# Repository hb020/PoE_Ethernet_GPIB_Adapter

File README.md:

# PoE Ethernet GPIB Adapter, with Prologix or VXI-11.2

## PoE-powered GPIB Adapter with Ethernet and USB-C Support

The **PoE Ethernet GPIB Adapter** is designed to interface test equipment with GPIB / HPIB / IEEE-488 interfaces.

The primary goal of this project is to provide an easy solution to connect multiple GPIB-equipped instruments over Ethernet without excessive cabling. It can, at choice, use the Prologix protocol or support VXI-11.2 (VISA).

---

## Why?

The motivation behind this project comes from the challenges of using several generations of instruments with GPIB interfaces. In theory, only one GPIB master is needed, and up to 20+ instruments can be connected in any order using suitable GPIB cabling. However, there are drawbacks:

- Instruments must be fully compliant with the IEEE-488 standard. Many older instruments, predating the standard, do not comply. The main issue is that the bus does not go Hi-Z when off, requiring certain instruments to be powered on even if you're only using another device.
- GPIB cabling is bulky and expensive. While used options can sometimes be found, the overall cost remains high.

At work, this has been solved elegantly using commercial Ethernet adapters, each assigned an address and connected directly to the instrument. However, these adapters are priced around $500 USD—far from hobbyist-friendly. My initial solution was to buy one adapter and rely on daisy-chaining, but as my instrument collection grew to 20 devices requiring GPIB, this approach was no longer practical. Hence, the **PoE Ethernet GPIB Adapter** was born.

---

## Design Criteria

1. Lower cost: Total BOM should be less than 50 USD.
2. Support Power over Ethernet (PoE) to minimize cable clutter.
3. Include USB-C power as an alternative if PoE is unavailable.
4. Enable GPIB communication over both Ethernet and USB-C interfaces.
5. Use the same communication protocol as existing commercial units.
6. Minimize radiated and conducted noise to avoid interference in test environments.
7. Include a simple, easy-to-print 3D-printed enclosure to keep costs low.

---

## Results

All design goals have been met[^2]. The current unit price is approximately $45 USD when ordering parts for 20 units. Prices increase for smaller batch sizes.

[^2]: GPIB commands over USB-C is Work In Progress.

In my home lab, I assign each device a static IP address based on its MAC address and run a local DNS server to provide easy-to-remember domain names, making the adapter simple and intuitive to use.

Project's documentation:

- [Design Documentation](docs/dn.md)
- [Design Test Documentation](docs/dt.md)

---

## VXI-11 or Prologix

This code can produce either a VXI-11.2 device, or a Prologix device (the ROM is not big enough for both at the same time, although the code is compatible with cohabitation). Switching between VXI-11 and Prologix is done at compile time. If compiler option `-DINTERFACE_PROLOGIX` is used, the firmware produced is for Prologix.

VXI-11.2 allows discovery over the network, and uses the following VISA connection strings:

- Controller[^1]: `TCPIP::{IP address}::INSTR` (unless you have set the default instrument address to something else than 0)
- Instruments: `TCPIP::{IP address}::gpib,N::INSTR` or `TCPIP::{IP address}::instN::INSTR`, where `N` is their address on the GPIB bus (1..30)

Example: `TCPIP::192.168.7.105::gpib,2::INSTR` for instrument with GPIB address 2 on the gateway having IP address 192.168.7.105.

[^1]: controller, gateway, adapter: different names for the same.

### VXI-11.2 compatibility

With the limited resources, this device is meant to work with the most common tools, like for example pyVisa. It is not a full implementation, and lacks the following advanced features:

- secondary instrument addresses
- async VXI-11 operations
- instrument locking via VXI-11
- VXI-11 interrupts
- the VXI-11 abort channel

It is discoverable via UDP, but there is no publication via mDNS (yet).

---

## The number of instruments you can connect

The GPIB bus protocol itself allows up to 30 instruments. This does not mean you can connect 30 instruments to the gateway, as the gateway device has its electrical limits, depending on the length of the cables and instruments themselves. And also the software has its limits.

The Prologix service will accept as many instruments as the gateway hardware can drive reliably.

The VXI-11 service is easier to integrate with many tools, but it consumes more resources on the gateway. The Ethernet chip can only maintain a limited number of network sockets, and each instrument requires a separate socket with VXI-11. Prologix uses only 1 socket, no matter the number of instruments. This means that regardless of the limitations of the hardware, there is a limit to the number of instruments you can connect to via VXI-11 compatible client software:

- up to 4 instruments: no restriction
- 5 instruments: only if you do not use the web server
- 6 instruments: only if you disable the web server (use the compile option `-DDISABLE_WEB_SERVER`)
- 7 or more: not possible via VXI-11

This does not mean that you cannot physically connect more instruments to the gateway, it just means that you cannot connect to more of them, via your client software, at the same time.

Also, be aware that the GPIB bus is a shared bus. Do not try to control instruments on the bus from different software clients at the same time. VXI-11 is somewhat more forgiving in this matter, but the prologix service simply doesn't allow multiple connections.

---

## The User Interface of the device

There are 3 parts:

- the **LED**. It indicates different states: blue for waiting for DHCP, red for error in network or DHCP, green flashing for idle, green/blue flashing for busy
- the **Web Server** (on port 80): it shows some help texts and the number of connected clients. It is not interactive.
- the **serial console** (via USB): This console shows startup information, ports used, and has a small menu. 

### The serial menu

This menu is rather basic. Be aware that it requires 'enter' for each command.

It has the following options:

- Setting of IP address. By default, the device starts with DHCP. You can however force a fixed IP address.
- Setting of the default instrument address (only with VXI-11, as Prologix has its own command for that). The default is 0, meaning: the gateway itself. If you only have 1 instrument connected, or want to designate a "preferred" instrument, you can set it to the address of any instrument on the bus. That way, the gateway becomes transparent, and you can use the default (and the discoverable) VISA connection string to address that instrument.

---

## Project files

Latest version is avaiable under [Releases](https://github.com/Kofen/PoE_Ethernet_GPIB_Adapter/releases)

And all the source code for all the parts should be in their respective folders in the repro. If anything is missing, let me know!

## How to compile

The easiest is for compilation with PlatformIO, from the [SW](/SW) directory.

## License

This project is licensed under the GPL V3. See the [LICENSE](LICENSE) file for details.

## Acknowledgements

- A huge thanks to the [AR488 project](https://github.com/Twilight-Logic/AR488), run by [Twilight-Logic](https://github.com/Twilight-Logic) and its community contributors. The current software is a fork of AR488. For more information about this, see [here](SW/README.md).

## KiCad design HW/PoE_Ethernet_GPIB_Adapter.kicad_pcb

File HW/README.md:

# PoE Ethernet GPIB Adapter - Hardware Files

## Overview

This folder contains the necessary hardware files for the PoE Ethernet GPIB Adapter project.

- **Schematics:** The schematic files can be found [here](https://github.com/Kofen/PoE_Ethernet_GPIB_Adapter/blob/main/HW/Schematic_PDF/PoE_Ethernet_GPIB_Adapter.pdf).
- **Output Files:** The output files, including Gerber files and assembly information, are located [here](https://github.com/Kofen/PoE_Ethernet_GPIB_Adapter/tree/main/HW/PoE_Ethernet_GPIB_Adapter_PCBA_MFG_Files).
- **Releases:** Precompiled hardware files for different versions are available under [Releases](https://github.com/Kofen/PoE_Ethernet_GPIB_Adapter/releases).

**Important note:** PCB thickness should be 1.6mm, 1 oz / 35 um copper thickness on all layers!

---

Ensure to verify compatibility with your PCB manufacturing service before using the files.

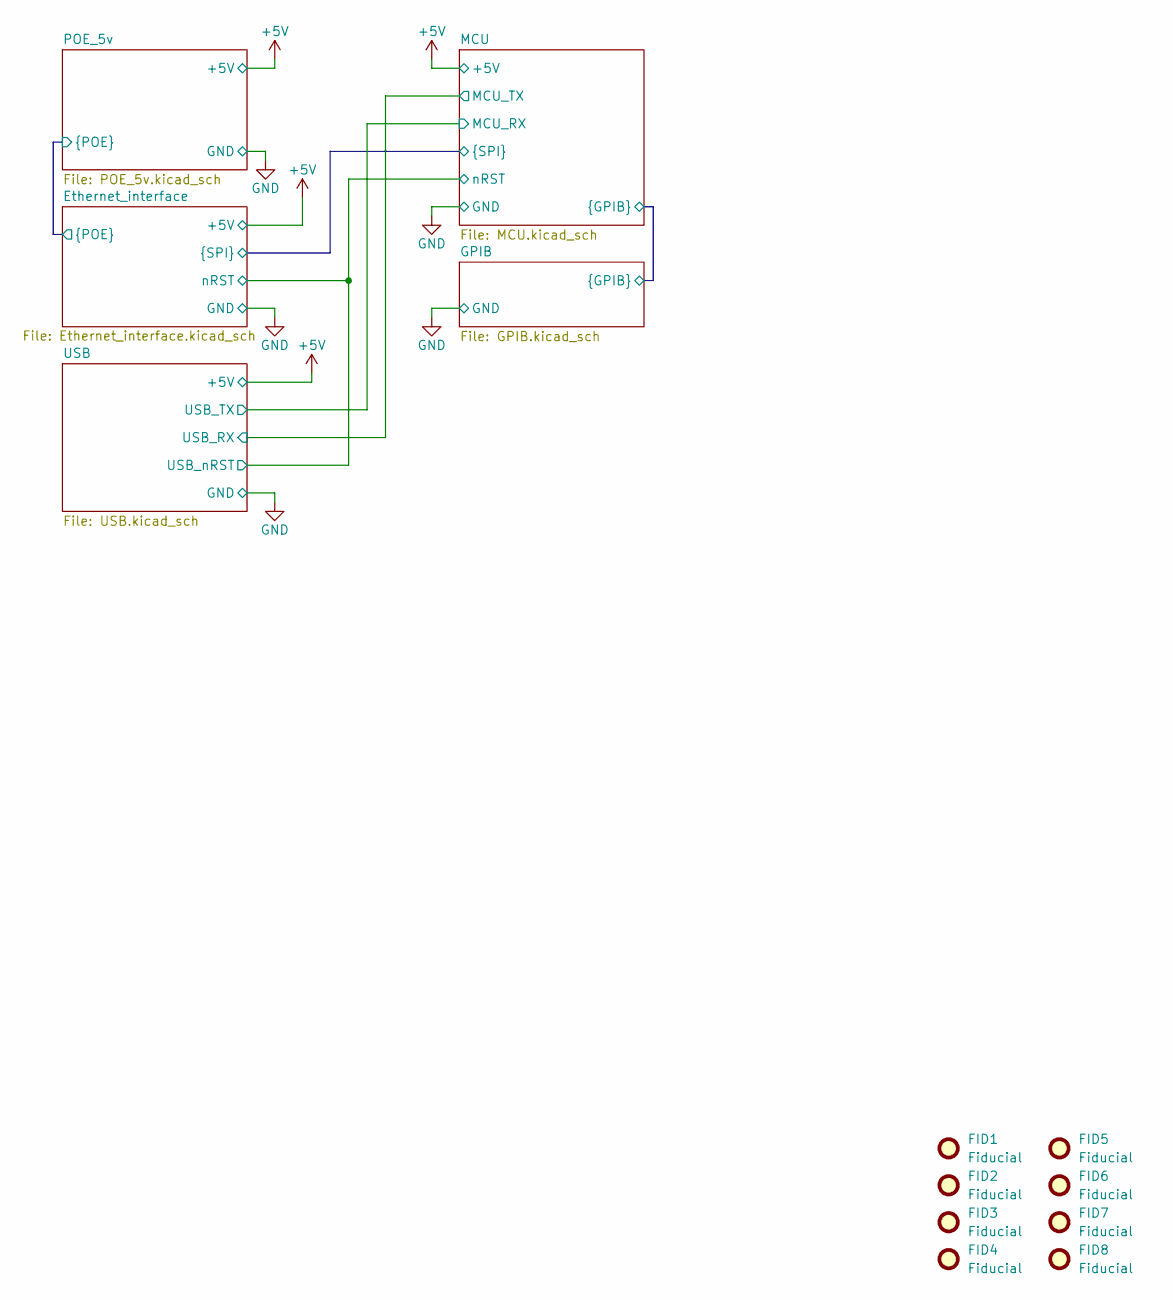
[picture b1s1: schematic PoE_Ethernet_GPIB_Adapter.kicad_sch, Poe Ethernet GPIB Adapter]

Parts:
FID1, FID2, FID3, FID4, FID5, FID6, FID7, FID8: Fiducial; Fiducial_0.75mm_Mask1.5mm

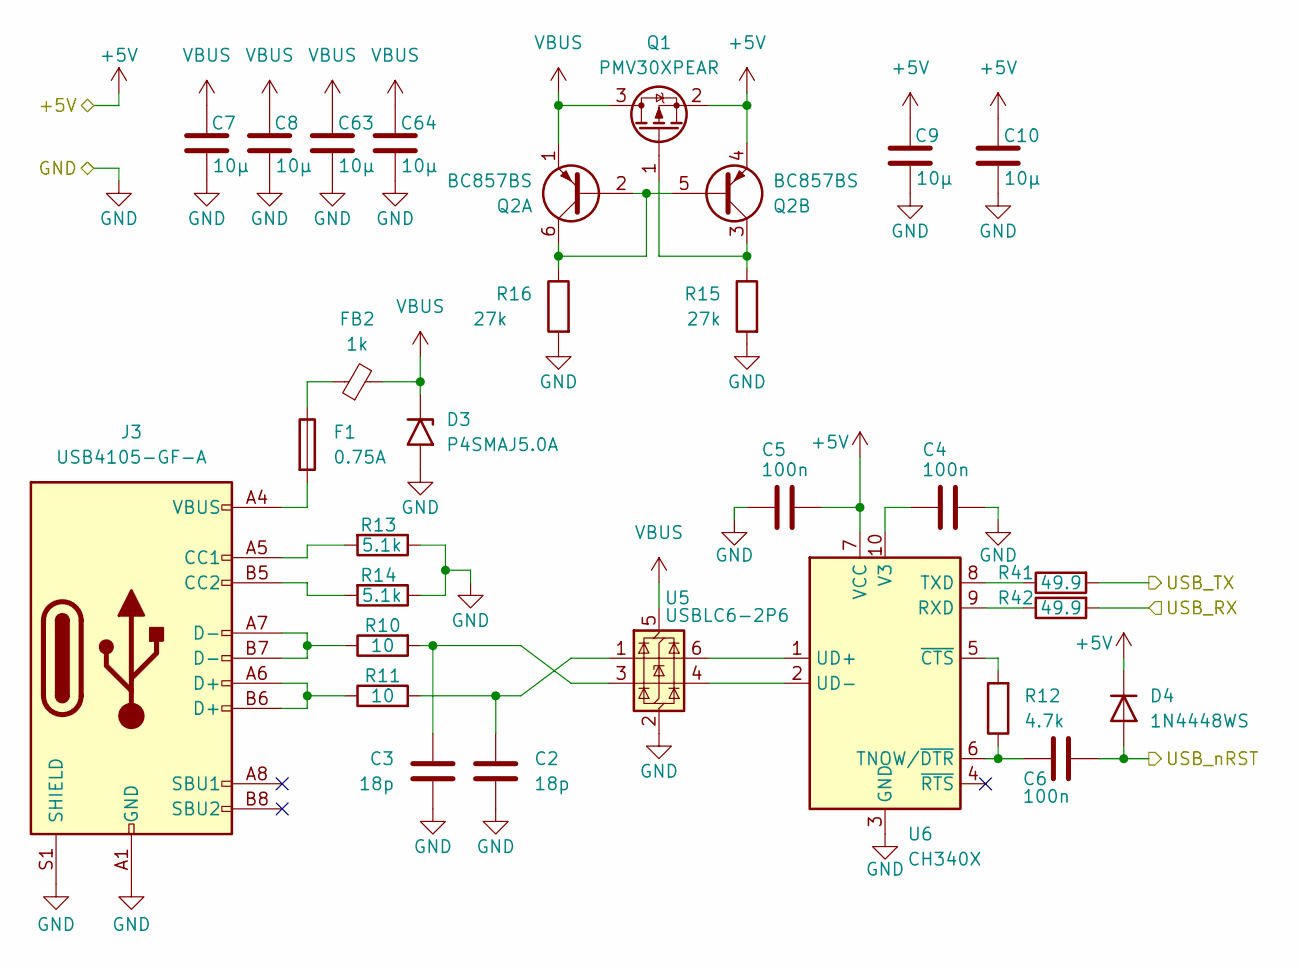
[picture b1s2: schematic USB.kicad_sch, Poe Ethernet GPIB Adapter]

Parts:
C2, C3: 18p; C_0402_1005Metric; JLCPCB C1549
C4, C5, C6: 100n; C_0402_1005Metric; JLCPCB C1525
C7, C8, C9, C10, C63, C64: 10µ; C_0402_1005Metric; JLCPCB C15525
D3: P4SMAJ5.0A; D_SMA; JLCPCB C391580
D4: 1N4448WS; D_SOD-323; JLCPCB C8602
F1: 0.75A; Fuse_1812_4532Metric; JLCPCB C3107
FB2: 1k; L_0805_2012Metric; JLCPCB C710395
J3: USB4105-GF-A; USB_C_Receptacle_GCT_USB4105-xx-A_16P_TopMnt_Horizontal; JLCPCB C3020560
Q1: PMV30XPEAR; SOT-23
Q2: BC857BS; SOT-363_SC-70-6
R10, R11: 10; R_0402_1005Metric
R12: 4.7k; R_0402_1005Metric
R13, R14: 5.1k; R_0402_1005Metric
R15, R16: 27k; R_0402_1005Metric
R41, R42: 49.9; R_0402_1005Metric
U5: USBLC6-2P6; SOT-666; JLCPCB C2827693
U6: CH340X; MSOP-10_3x3mm_P0.5mm; JLCPCB C3035748

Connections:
+5V: C5.2, C9.1, C10.1, D4.1 (K), Q1.2 (S), Q2.4 (E2), U6.7 (VCC); also elsewhere on the board
/Ethernet_interface/nRST: C6.2, D4.2 (A); also elsewhere on the board
/MCU/MCU_RX: R41.2; also elsewhere on the board
/MCU/MCU_TX: R42.2; also elsewhere on the board
GND: C2.2, C3.2, C4.2, C5.1, C7.2, C8.2, C9.2, C10.2, C63.2, C64.2, D3.2 (A2), J3.A1 (GND), J3.A12 (GND), J3.B1 (GND), J3.B12 (GND), J3.S1 (SHIELD), R13.1, R14.1, R15.2, R16.2, U5.2 (GND), U6.3 (GND); also elsewhere on the board
unnamed: C2.1, R11.2, U5.1 (I/O1)
unnamed: C3.1, R10.2, U5.3 (I/O2)
unnamed: F1.1, FB2.1
unnamed: F1.2, J3.A4 (VBUS), J3.A9 (VBUS), J3.B4 (VBUS), J3.B9 (VBUS)
unnamed: J3.A5 (CC1), R13.2
unnamed: J3.B5 (CC2), R14.2
unnamed: J3.A6 (D+), J3.B6 (D+), R11.1
unnamed: J3.A7 (D-), J3.B7 (D-), R10.1
unnamed: Q1.1 (G), Q2.3 (C2), R15.1
unnamed: Q2.2 (B1), Q2.5 (B2), Q2.6 (C1), R16.1
unnamed: R42.1, U6.9 (RXD)
unnamed: C6.1, R12.1, U6.6 (TNOW/~DTR)
unnamed: R41.1, U6.8 (TXD)
unnamed: U5.6 (I/O1), U6.1 (UD+)
unnamed: U5.4 (I/O2), U6.2 (UD-)
unnamed: C4.1, U6.10 (V3)
unnamed: R12.2, U6.5 (~CTS)
VBUS: C7.1, C8.1, C63.1, C64.1, D3.1 (A1), FB2.2, Q1.3 (D), Q2.1 (E1), U5.5 (VBUS)

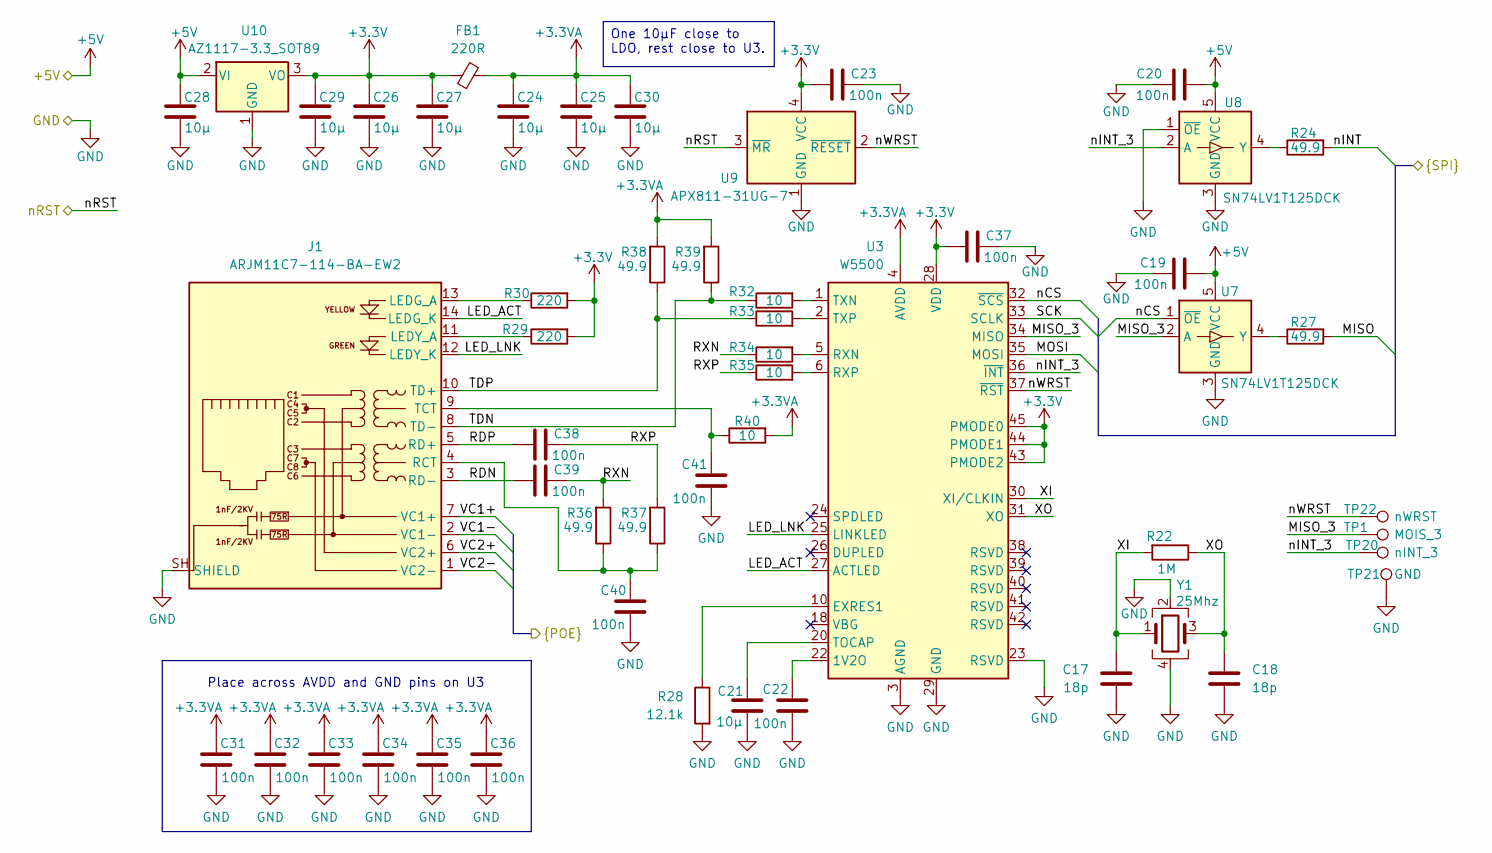
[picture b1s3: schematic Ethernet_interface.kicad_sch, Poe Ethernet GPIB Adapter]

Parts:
C17, C18: 18p; C_0402_1005Metric; JLCPCB C1549
C19, C20, C22, C23, C31, C32, C33, C34, C35, C36, C37, C38, C39, C40, C41: 100n; C_0402_1005Metric; JLCPCB C1525
C21, C24, C25, C26, C27, C28, C29, C30: 10µ; C_0402_1005Metric; JLCPCB C15525
FB1: 220R; L_0603_1608Metric; JLCPCB C139471
J1: ARJM11C7-114-BA-EW2; RJ45_ARJM11C7-114-BA-EW2
R22: 1M; R_0402_1005Metric
R24, R27, R36, R37, R38, R39: 49.9; R_0402_1005Metric
R28: 12.1k; R_0402_1005Metric
R29, R30: 220; R_0402_1005Metric
R32, R33, R34, R35, R40: 10; R_0402_1005Metric
TP1: MOIS_3; TestPoint_Pad_D1.0mm
TP20: nINT_3; TestPoint_Pad_D1.0mm
TP21: GND; TestPoint_Pad_D1.0mm
TP22: nWRST; TestPoint_Pad_D1.0mm
U3: W5500; LQFP-48_7x7mm_P0.5mm; JLCPCB C32843
U7, U8: SN74LV1T125DCK; SOT-353_SC-70-5; JLCPCB C2859742
U9: APX811-31UG-7; SOT-143; JLCPCB C150481
U10: AZ1117-3.3_SOT89; SOT-89-3; JLCPCB C362111
Y1: 25Mhz; Crystal_SMD_2520-4Pin_2.5x2.0mm; JLCPCB C5727305

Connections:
+3.3V: C23.2, C26.1, C27.1, C29.1, C37.2, FB1.1, R29.2, R30.2, U3.28 (VDD), U3.43 (PMODE2), U3.44 (PMODE1), U3.45 (PMODE0), U9.4 (VCC), U10.3 (VO)
+3.3VA: C24.1, C25.1, C30.1, C31.2, C32.2, C33.2, C34.2, C35.2, C36.2, FB1.2, R38.2, R39.2, R40.2, U3.4 (AVDD), U3.8 (AVDD), U3.11 (AVDD), U3.15 (AVDD), U3.17 (AVDD), U3.21 (AVDD)
+5V: C19.2, C20.2, C28.1, U7.5 (VCC), U8.5 (VCC), U10.2 (VI); also elsewhere on the board
/Ethernet_interface/LED_ACT: J1.14 (LEDG_K), U3.27 (ACTLED)
/Ethernet_interface/LED_LNK: J1.12 (LEDY_K), U3.25 (LINKLED)
/Ethernet_interface/MISO: R27.2; also elsewhere on the board
/Ethernet_interface/MISO_3: TP1.1, U3.34 (MISO), U7.2 (A)
/Ethernet_interface/MOSI: U3.35 (MOSI); also elsewhere on the board
/Ethernet_interface/RDN: C39.2, J1.3 (RD-)
/Ethernet_interface/RDP: C38.2, J1.5 (RD+)
/Ethernet_interface/RXN: C39.1, R34.1, R36.2
/Ethernet_interface/RXP: C38.1, R35.1, R37.2
/Ethernet_interface/SCK: U3.33 (SCLK); also elsewhere on the board
/Ethernet_interface/TDN: J1.8 (TD-), R32.1, R39.1
/Ethernet_interface/TDP: J1.10 (TD+), R33.1, R38.1
/Ethernet_interface/VC1+: J1.7 (VC1+); also elsewhere on the board
/Ethernet_interface/VC1-: J1.2 (VC1-); also elsewhere on the board
/Ethernet_interface/VC2+: J1.6 (VC2+); also elsewhere on the board
/Ethernet_interface/VC2-: J1.1 (VC2-); also elsewhere on the board
/Ethernet_interface/XI: C17.1, R22.2, U3.30 (XI/CLKIN), Y1.1
/Ethernet_interface/XO: C18.1, R22.1, U3.31 (XO), Y1.3
/Ethernet_interface/nCS: U3.32 (~SCS), U7.1 (~OE); also elsewhere on the board
/Ethernet_interface/nINT: R24.2; also elsewhere on the board
/Ethernet_interface/nINT_3: TP20.1, U3.36 (~INT), U8.2 (A)
/Ethernet_interface/nRST: U9.3 (~MR); also elsewhere on the board
/Ethernet_interface/nWRST: TP22.1, U3.37 (~RST), U9.2 (~RESET)
GND: C17.2, C18.2, C19.1, C20.1, C21.2, C22.1, C23.1, C24.2, C25.2, C26.2, C27.2, C28.2, C29.2, C30.2, C31.1, C32.1, C33.1, C34.1, C35.1, C36.1, C37.1, C40.1, C41.1, J1.SH (SHIELD), R28.2, TP21.1, U3.3 (AGND), U3.9 (AGND), U3.14 (AGND), U3.16 (AGND), U3.19 (AGND), U3.23 (RSVD), U3.29 (GND), U3.48 (AGND), U7.3 (GND), U8.1 (~OE), U8.3 (GND), U9.1 (GND), U10.1 (GND), Y1.2, Y1.4; also elsewhere on the board
unnamed: J1.13 (LEDG_A), R30.1
unnamed: J1.11 (LEDY_A), R29.1
unnamed: C40.2, J1.4 (RCT), R36.1, R37.1
unnamed: C41.2, J1.9 (TCT), R40.1
unnamed: C22.2, U3.22 (1V2O)
unnamed: R28.1, U3.10 (EXRES1)
unnamed: R34.2, U3.5 (RXN)
unnamed: R35.2, U3.6 (RXP)
unnamed: C21.1, U3.20 (TOCAP)
unnamed: R32.2, U3.1 (TXN)
unnamed: R33.2, U3.2 (TXP)
unnamed: R27.1, U7.4 (Y)
unnamed: R24.1, U8.4 (Y)

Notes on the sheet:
Place across AVDD and GND pins on U3
One 10µF close to LDO, rest close to U3.

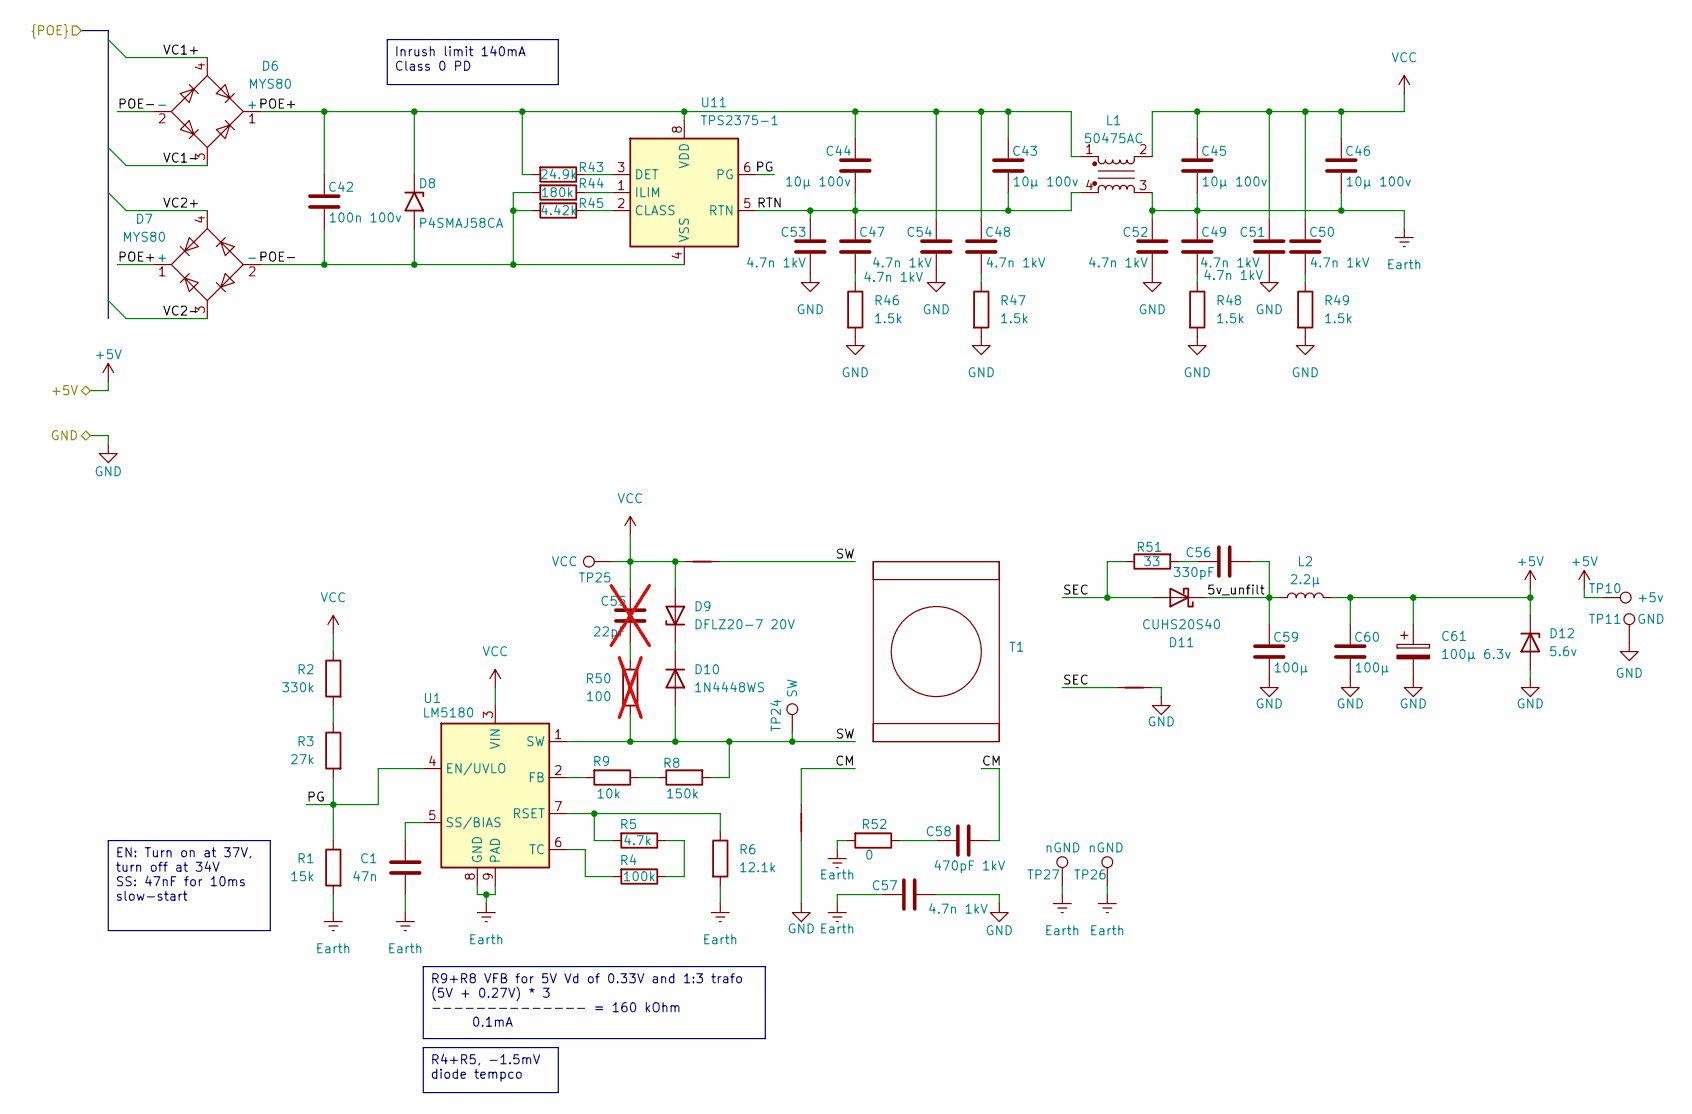
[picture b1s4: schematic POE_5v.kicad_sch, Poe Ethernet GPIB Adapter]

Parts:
C1: 47n; C_0402_1005Metric; JLCPCB C82219
C42: 100n 100v; C_0603_1608Metric; JLCPCB C15725
C43, C44, C45, C46: 10µ 100v; C_1210_3225Metric; JLCPCB C5156756
C47, C48, C49, C50, C51, C52, C53, C54, C57: 4.7n 1kV; C_0805_2012Metric; JLCPCB C565695
C55: 22pF; C_0603_1608Metric; not fitted
C56: 330pF; C_0603_1608Metric; JLCPCB C458879
C58: 470pF 1kV; C_0805_2012Metric; JLCPCB C20416464
C59, C60: 100µ; C_1206_3216Metric; JLCPCB CL31A107MQHNNNE
C61: 100µ 6.3v; CP_Elec_5x5.3; JLCPCB C5530352
D6, D7: MYS80; Diode_Bridge_Diotec_MicroDil_3.0x3.0x1.8mm; JLCPCB C3589669
D8: P4SMAJ58CA; D_SMA; JLCPCB C268635
D9: DFLZ20-7 20V; D_PowerDI-123; JLCPCB C177024
D10: 1N4448WS; D_SOD-323; JLCPCB C8602
D11: CUHS20S40; D_TUMD2; JLCPCB C3758140
D12: 5.6v; D_SOD-123F; JLCPCB C2119
L1: 50475AC; muRata_5000A
L2: 2.2µ; L_Taiyo-Yuden_NR-50xx
NT1, NT2: NetTie_2; NetTie-2_SMD_Pad0.5mm
NT3: NetTie_2; NetTie-2_SMD_Pad0.8mm
R1: 15k; R_0402_1005Metric
R2: 330k; R_0805_2012Metric
R3: 27k; R_0402_1005Metric
R4: 100k; R_0402_1005Metric
R5: 4.7k; R_0402_1005Metric
R6: 12.1k; R_0402_1005Metric
R8: 150k; R_0805_2012Metric
R9: 10k; R_0402_1005Metric
R43: 24.9k; R_0402_1005Metric
R44: 180k; R_0402_1005Metric
R45: 4.42k; R_0402_1005Metric
R46, R47, R48, R49: 1.5k; R_0603_1608Metric
R50: 100; R_0603_1608Metric; not fitted
R51: 33; R_0603_1608Metric
R52: 0; R_0603_1608Metric
T1: ER14_planar_4_to_1_48v_in_5v_out_5w
TP10: +5v; TestPoint_Pad_D1.0mm
TP11: GND; TestPoint_Pad_D1.0mm
TP24: SW; TestPoint_Pad_D1.0mm
TP25: VCC; TestPoint_Pad_D1.0mm
TP26, TP27: nGND; TestPoint_Pad_D1.0mm
U1: LM5180; WSON-8-1EP_4x4mm_P0.8mm_EP1.98x3mm; JLCPCB C2868878
U11: TPS2375-1; TSSOP-8_4.4x3mm_P0.65mm; JLCPCB C2859774

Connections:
+5V: C60.1, C61.1, D12.1 (K), L2.2, TP10.1; also elsewhere on the board
/Ethernet_interface/VC1+: D6.4; also elsewhere on the board
/Ethernet_interface/VC1-: D6.3; also elsewhere on the board
/Ethernet_interface/VC2+: D7.4; also elsewhere on the board
/Ethernet_interface/VC2-: D7.3; also elsewhere on the board
/POE_5v/5v_unfilt: C56.2, C59.1, D11.1 (K), L2.1
/POE_5v/CM: C58.1, NT2.2
/POE_5v/PG: R1.1, R3.2, U1.4 (EN/UVLO), U11.6 (PG)
/POE_5v/POE+: C42.1, C43.1, C44.1, C48.1, C54.1, D6.1 (+), D7.1 (+), D8.1 (A1), L1.1, R43.2, U11.8 (VDD)
/POE_5v/POE-: C42.2, D6.2 (-), D7.2 (-), D8.2 (A2), R44.2, R45.2, U11.4 (VSS)
/POE_5v/RTN: C43.2, C44.2, C47.1, C53.1, L1.4, U11.5 (RTN)
/POE_5v/SEC: D11.2 (A), NT3.1, R51.1
/POE_5v/SW: D10.2 (A), NT1.2, R8.2, R50.2, TP24.1, U1.1 (SW)
Earth: C1.2, C45.2, C46.2, C49.1, C52.1, C57.2, L1.3, R1.2, R6.2, R52.2, TP26.1, TP27.1, U1.8 (GND), U1.9 (PAD)
GND: C51.2, C52.2, C53.2, C54.2, C57.1, C59.2, C60.2, C61.2, D12.2 (A), NT2.1, NT3.2, R46.2, R47.2, R48.2, R49.2, TP11.1; also elsewhere on the board
unnamed: C47.2, R46.1
unnamed: C48.2, R47.1
unnamed: C49.2, R48.1
unnamed: C50.2, R49.1
unnamed: C55.2, R50.1
unnamed: C56.1, R51.2
unnamed: C58.2, R52.1
unnamed: D9.1 (K), D10.1 (K)
unnamed: R2.2, R3.1
unnamed: R4.1, R5.1
unnamed: R8.1, R9.1
unnamed: R9.2, U1.2 (FB)
unnamed: R5.2, R6.1, U1.7 (RSET)
unnamed: C1.1, U1.5 (SS/BIAS)
unnamed: R4.2, U1.6 (TC)
unnamed: R45.1, U11.2 (CLASS)
unnamed: R43.1, U11.3 (DET)
unnamed: R44.1, U11.1 (ILIM)
VCC: C45.1, C46.1, C50.1, C51.1, C55.1, D9.2 (A), L1.2, NT1.1, R2.1, TP25.1, U1.3 (VIN)

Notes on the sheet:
R9+R8 VFB for 5V Vd of 0.33V and 1:3 trafo (5V + 0.27V) * 3 -------------- = 160 kOhm 0.1mA
R4+R5, -1.5mV diode tempco
EN: Turn on at 37V, turn off at 34V SS: 47nF for 10ms slow-start
Inrush limit 140mA Class 0 PD

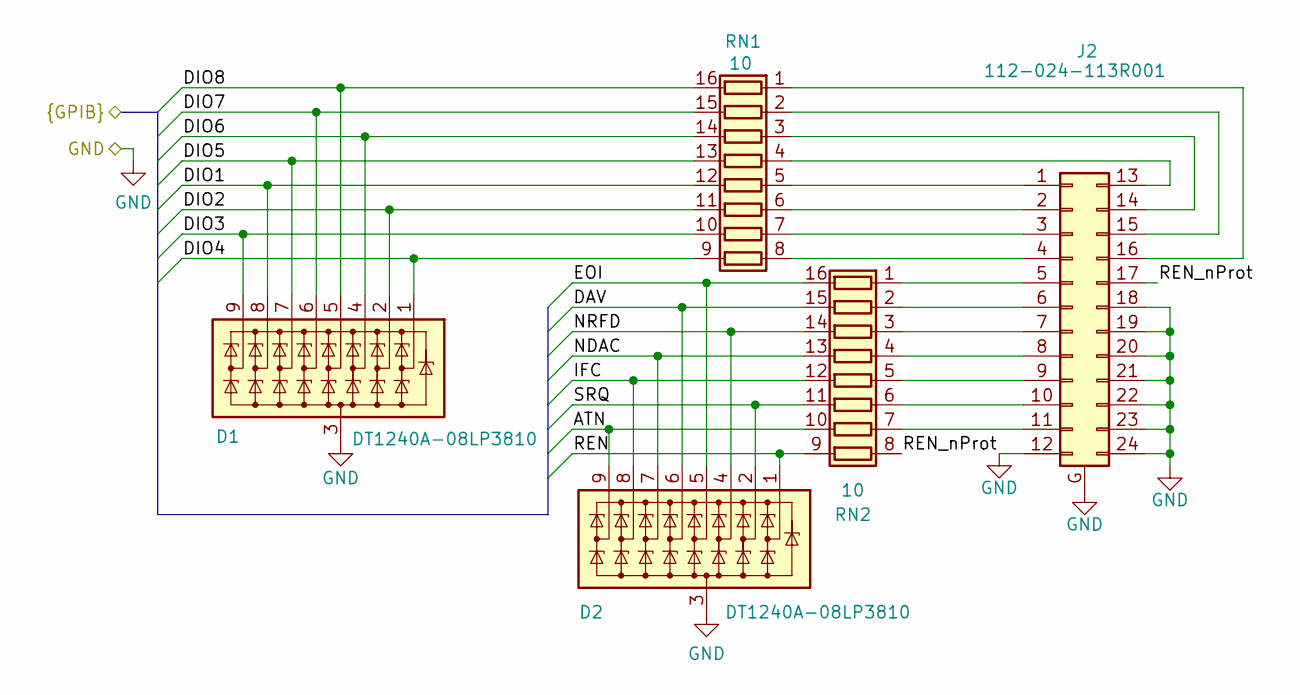
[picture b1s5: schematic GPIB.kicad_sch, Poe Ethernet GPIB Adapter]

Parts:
D1, D2: DT1240A-08LP3810; UDFN-9_1.0x3.8mm_P0.5mm; JLCPCB C526598
J2: 112-024-113R001
RN1, RN2: 10; R_Array_Convex_8x0602; JLCPCB C1518172

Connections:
/GPIB/ATN: D2.9 (K8), RN2.10 (R7.2); also elsewhere on the board
/GPIB/DAV: D2.6 (K5), RN2.15 (R2.2); also elsewhere on the board
/GPIB/DIO1: D1.8 (K7), RN1.12 (R5.2); also elsewhere on the board
/GPIB/DIO2: D1.2 (K2), RN1.11 (R6.2); also elsewhere on the board
/GPIB/DIO3: D1.9 (K8), RN1.10 (R7.2); also elsewhere on the board
/GPIB/DIO4: D1.1 (K1), RN1.9 (R8.2); also elsewhere on the board
/GPIB/DIO5: D1.7 (K6), RN1.13 (R4.2); also elsewhere on the board
/GPIB/DIO6: D1.4 (K3), RN1.14 (R3.2); also elsewhere on the board
/GPIB/DIO7: D1.6 (K5), RN1.15 (R2.2); also elsewhere on the board
/GPIB/DIO8: D1.5 (K4), RN1.16 (R1.2); also elsewhere on the board
/GPIB/EOI: D2.5 (K4), RN2.16 (R1.2); also elsewhere on the board
/GPIB/IFC: D2.8 (K7), RN2.12 (R5.2); also elsewhere on the board
/GPIB/NDAC: D2.7 (K6), RN2.13 (R4.2); also elsewhere on the board
/GPIB/NRFD: D2.4 (K3), RN2.14 (R3.2); also elsewhere on the board
/GPIB/REN: D2.1 (K1), RN2.9 (R8.2); also elsewhere on the board
/GPIB/REN_nProt: J2.17, RN2.8 (R8.1)
/GPIB/SRQ: D2.2 (K2), RN2.11 (R6.2); also elsewhere on the board
GND: D1.3 (A), D2.3 (A), J2.12, J2.18, J2.19, J2.20, J2.21, J2.22, J2.23, J2.24, J2.G (Chassis); also elsewhere on the board
unnamed: J2.1, RN1.5 (R5.1)
unnamed: J2.2, RN1.6 (R6.1)
unnamed: J2.3, RN1.7 (R7.1)
unnamed: J2.4, RN1.8 (R8.1)
unnamed: J2.5, RN2.1 (R1.1)
unnamed: J2.6, RN2.2 (R2.1)
unnamed: J2.7, RN2.3 (R3.1)
unnamed: J2.8, RN2.4 (R4.1)
unnamed: J2.9, RN2.5 (R5.1)
unnamed: J2.10, RN2.6 (R6.1)
unnamed: J2.11, RN2.7 (R7.1)
unnamed: J2.13, RN1.4 (R4.1)
unnamed: J2.14, RN1.3 (R3.1)
unnamed: J2.15, RN1.2 (R2.1)
unnamed: J2.16, RN1.1 (R1.1)

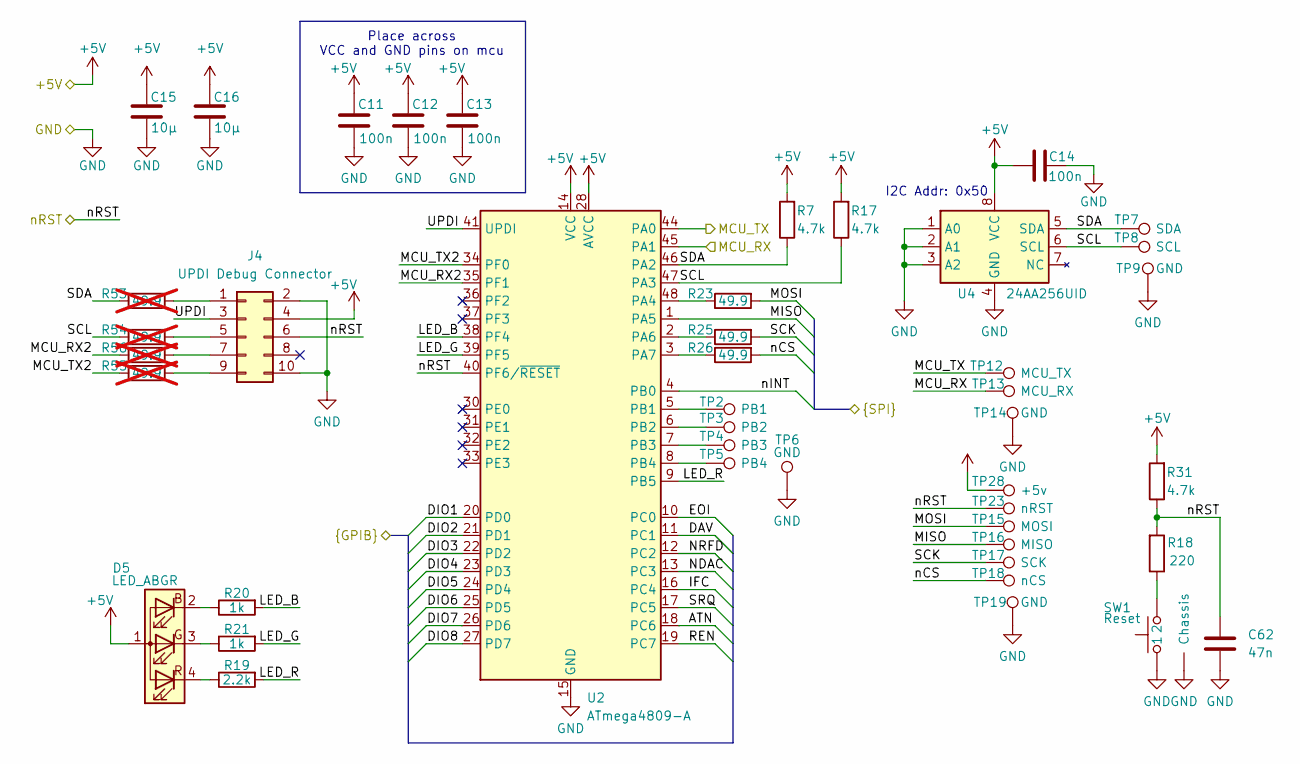
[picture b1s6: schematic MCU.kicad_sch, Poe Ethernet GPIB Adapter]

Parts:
C11, C12, C13, C14: 100n; C_0402_1005Metric; JLCPCB C1525
C15, C16: 10µ; C_0402_1005Metric; JLCPCB C15525
C62: 47n; C_0402_1005Metric; JLCPCB C82219
D5: LED_ABGR; LED_RGB_Everlight_EASV3015RGBA0_Horizontal; JLCPCB C5365900
J4: UPDI Debug Connector; PinHeader_2x05_P1.27mm_Vertical
R7, R17, R31: 4.7k; R_0402_1005Metric
R18: 220; R_0402_1005Metric
R19: 2.2k; R_0402_1005Metric
R20, R21: 1k; R_0402_1005Metric
R23, R25, R26: 49.9; R_0402_1005Metric
R53, R54, R55, R56: 49.9; R_0402_1005Metric; not fitted
SW1: Reset; SW_Tactile_SKHH_Angled
TP2: PB1; TestPoint_Pad_D1.0mm
TP3: PB2; TestPoint_Pad_D1.0mm
TP4: PB3; TestPoint_Pad_D1.0mm
TP5: PB4; TestPoint_Pad_D1.0mm
TP6, TP9, TP14, TP19: GND; TestPoint_Pad_D1.0mm
TP7: SDA; TestPoint_Pad_D1.0mm
TP8: SCL; TestPoint_Pad_D1.0mm
TP12: MCU_TX; TestPoint_Pad_D1.0mm
TP13: MCU_RX; TestPoint_Pad_D1.0mm
TP15: MOSI; TestPoint_Pad_D1.0mm
TP16: MISO; TestPoint_Pad_D1.0mm
TP17: SCK; TestPoint_Pad_D1.0mm
TP18: nCS; TestPoint_Pad_D1.0mm
TP23: nRST; TestPoint_Pad_D1.0mm
TP28: +5v; TestPoint_Pad_D1.0mm
U2: ATmega4809-A; TQFP-48_7x7mm_P0.5mm; JLCPCB C1340041
U4: 24AA256UID; SOIC-8_3.9x4.9mm_P1.27mm; JLCPCB C1349800

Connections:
+5V: C11.2, C12.2, C13.2, C14.1, C15.1, C16.1, D5.1 (A), J4.4, R7.2, R17.2, R31.2, TP28.1, U2.14 (VCC), U2.28 (AVCC), U2.42 (VCC), U4.8 (VCC); also elsewhere on the board
/Ethernet_interface/MISO: TP16.1, U2.1 (PA5); also elsewhere on the board
/Ethernet_interface/MOSI: R23.2, TP15.1; also elsewhere on the board
/Ethernet_interface/SCK: R25.2, TP17.1; also elsewhere on the board
/Ethernet_interface/nCS: R26.2, TP18.1; also elsewhere on the board
/Ethernet_interface/nINT: U2.4 (PB0); also elsewhere on the board
/Ethernet_interface/nRST: C62.1, J4.6, R18.2, R31.1, TP23.1, U2.40 (PF6/~RESET); also elsewhere on the board
/GPIB/ATN: U2.18 (PC6); also elsewhere on the board
/GPIB/DAV: U2.11 (PC1); also elsewhere on the board
/GPIB/DIO1: U2.20 (PD0); also elsewhere on the board
/GPIB/DIO2: U2.21 (PD1); also elsewhere on the board
/GPIB/DIO3: U2.22 (PD2); also elsewhere on the board
/GPIB/DIO4: U2.23 (PD3); also elsewhere on the board
/GPIB/DIO5: U2.24 (PD4); also elsewhere on the board
/GPIB/DIO6: U2.25 (PD5); also elsewhere on the board
/GPIB/DIO7: U2.26 (PD6); also elsewhere on the board
/GPIB/DIO8: U2.27 (PD7); also elsewhere on the board
/GPIB/EOI: U2.10 (PC0); also elsewhere on the board
/GPIB/IFC: U2.16 (PC4); also elsewhere on the board
/GPIB/NDAC: U2.13 (PC3); also elsewhere on the board
/GPIB/NRFD: U2.12 (PC2); also elsewhere on the board
/GPIB/REN: U2.19 (PC7); also elsewhere on the board
/GPIB/SRQ: U2.17 (PC5); also elsewhere on the board
/MCU/LED_B: R20.2, U2.38 (PF4)
/MCU/LED_G: R21.2, U2.39 (PF5)
/MCU/LED_R: R19.2, U2.9 (PB5)
/MCU/MCU_RX: TP13.1, U2.45 (PA1); also elsewhere on the board
/MCU/MCU_RX2: R56.1, U2.35 (PF1)
/MCU/MCU_TX: TP12.1, U2.44 (PA0); also elsewhere on the board
/MCU/MCU_TX2: R55.1, U2.34 (PF0)
/MCU/SCL: R17.1, R54.1, TP8.1, U2.47 (PA3), U4.6 (SCL)
/MCU/SDA: R7.1, R53.1, TP7.1, U2.46 (PA2), U4.5 (SDA)
/MCU/UPDI: J4.3, U2.41 (UPDI)
GND: C11.1, C12.1, C13.1, C14.2, C15.2, C16.2, C62.2, J4.2, J4.10, SW1.1, SW1.G (Chassis), TP6.1, TP9.1, TP14.1, TP19.1, U2.15 (GND), U2.29 (GND), U2.43 (GND), U4.1 (A0), U4.2 (A1), U4.3 (A2), U4.4 (GND); also elsewhere on the board
unnamed: D5.2 (BK), R20.1
unnamed: D5.3 (GK), R21.1
unnamed: D5.4 (RK), R19.1
unnamed: J4.1, R53.2
unnamed: J4.5, R54.2
unnamed: J4.7, R56.2
unnamed: J4.9, R55.2
unnamed: R18.1, SW1.2
unnamed: R23.1, U2.48 (PA4)
unnamed: R25.1, U2.2 (PA6)
unnamed: R26.1, U2.3 (PA7)
unnamed: TP2.1, U2.5 (PB1)
unnamed: TP3.1, U2.6 (PB2)
unnamed: TP4.1, U2.7 (PB3)
unnamed: TP5.1, U2.8 (PB4)

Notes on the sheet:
I2C Addr: 0x50
Place across VCC and GND pins on mcu

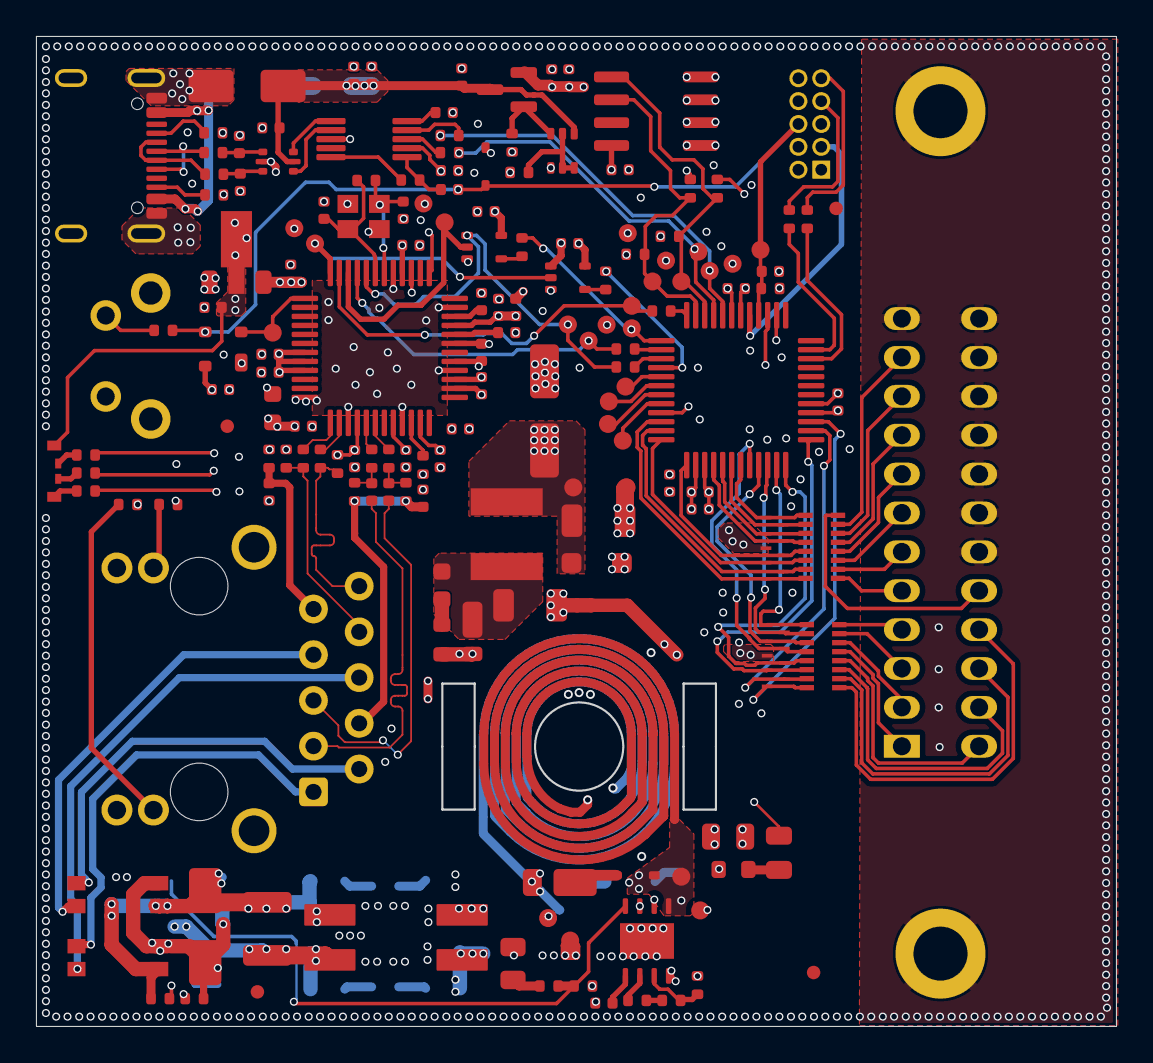
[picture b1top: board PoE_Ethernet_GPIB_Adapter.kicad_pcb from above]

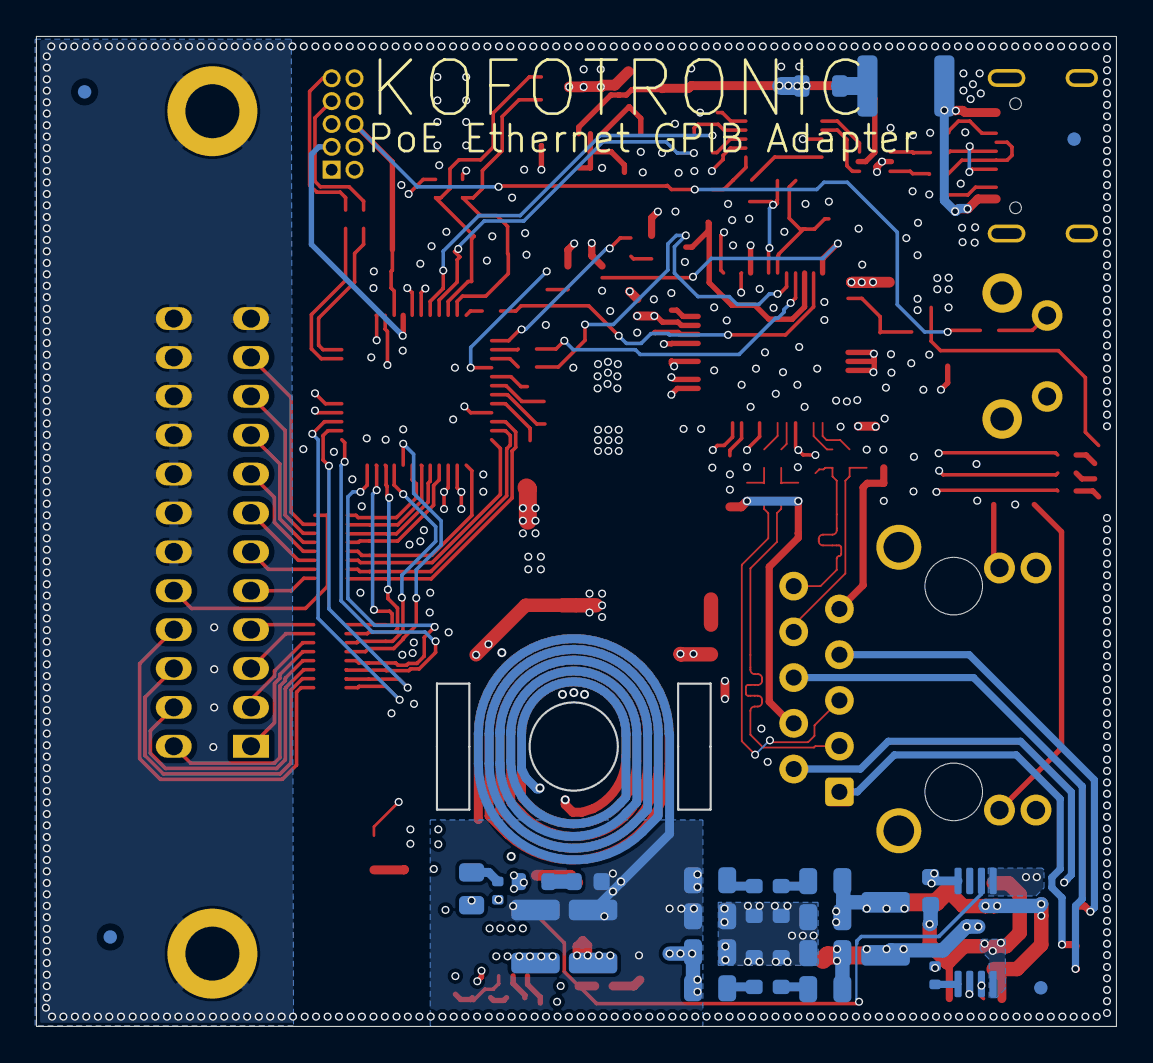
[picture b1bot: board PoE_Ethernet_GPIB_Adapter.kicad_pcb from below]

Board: 6 copper layers, 60.0 x 55.0 mm, 198 parts (29 on the bottom side), 143 nets.

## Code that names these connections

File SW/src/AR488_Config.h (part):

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
#ifdef AR488_CUSTOM

#define DIO1_PIN  22  /*PD0 GPIB 1  */
#define DIO2_PIN  23  /*PD1 GPIB 2  */
#define DIO3_PIN  24  /*PD2 GPIB 3  */
#define DIO4_PIN  25  /*PD3 GPIB 4  */
#define DIO5_PIN  26  /*PD4 GPIB 13 */
#define DIO6_PIN  27  /*PD5 GPIB 14 */
#define DIO7_PIN  28  /*PD6 GPIB 15 */
#define DIO8_PIN  29  /*PD7 GPIB 16 */

#define EOI_PIN   14  /*PC0 GPIB 5  */
#define DAV_PIN   15  /*PC1 GPIB 6  */
#define NRFD_PIN  16  /*PC2 GPIB 7  */
#define NDAC_PIN  17  /*PC3 GPIB 8  */
#define IFC_PIN   18  /*PC4 GPIB 9  */
#define SRQ_PIN   19  /*PC5 GPIB 10 */
#define ATN_PIN   20  /*PC6 GPIB 11 */
#define REN_PIN   21  /*PC7 GPIB 17 */


/*
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
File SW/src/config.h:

#pragma once

#define DEVICE_NAME "Ethernet2GPIB Gateway v1.1 (AR488 v0.53.03)\n"

#define LED_R 13
#define LED_G 39
#define LED_B 38

// This is needed, and debugPort should point to Serial if you want to use the serial menu
#define DEBUG_ENABLE
// define USE_SERIALMENU if you want a basic menu on the serial console. Unfortunately, this library is hardcoded to use Serial.
#define USE_SERIALMENU

// define USE_WEBSERVER if you want to use a very basic web page server that serves a static explanation page.
// It is not interactive, just a cherry on the cake.
// This is meant to be used with the VXI server, but it might work with the Prologix server too.
#define USE_WEBSERVER

#ifndef INTERFACE_PROLOGIX
#define INTERFACE_VXI11
#endif
// and if you define both, well, you'll have to deal with the compiler telling you there is not enough ROM.


// for the Prologix server: 
#define AR_ETHERNET_PORT
#define PROLOGIX_PORT 1234

// For the VXI server:
#define VXI11_PORT 9010
#define MAX_VXI_CLIENTS 30
// set LOG_VXI_DETAILS to 0 or 1, depending on whether you want to see VXI details on the debugPort
// setting to 1 messes up the serial menu a bit
#define LOG_VXI_DETAILS 1

// if you acticate this, the serial menu will be messier. 
// Only activate this when you want to see memory usage 
// and other details in auto refresh on the console.
// #define LOG_STATS_ON_CONSOLE

// EEPROM use: 
// Writing the 24AA256 is somehow broken, so we can also write via the GPIB configuration
#define AR488_GPIBconf_EXTEND
